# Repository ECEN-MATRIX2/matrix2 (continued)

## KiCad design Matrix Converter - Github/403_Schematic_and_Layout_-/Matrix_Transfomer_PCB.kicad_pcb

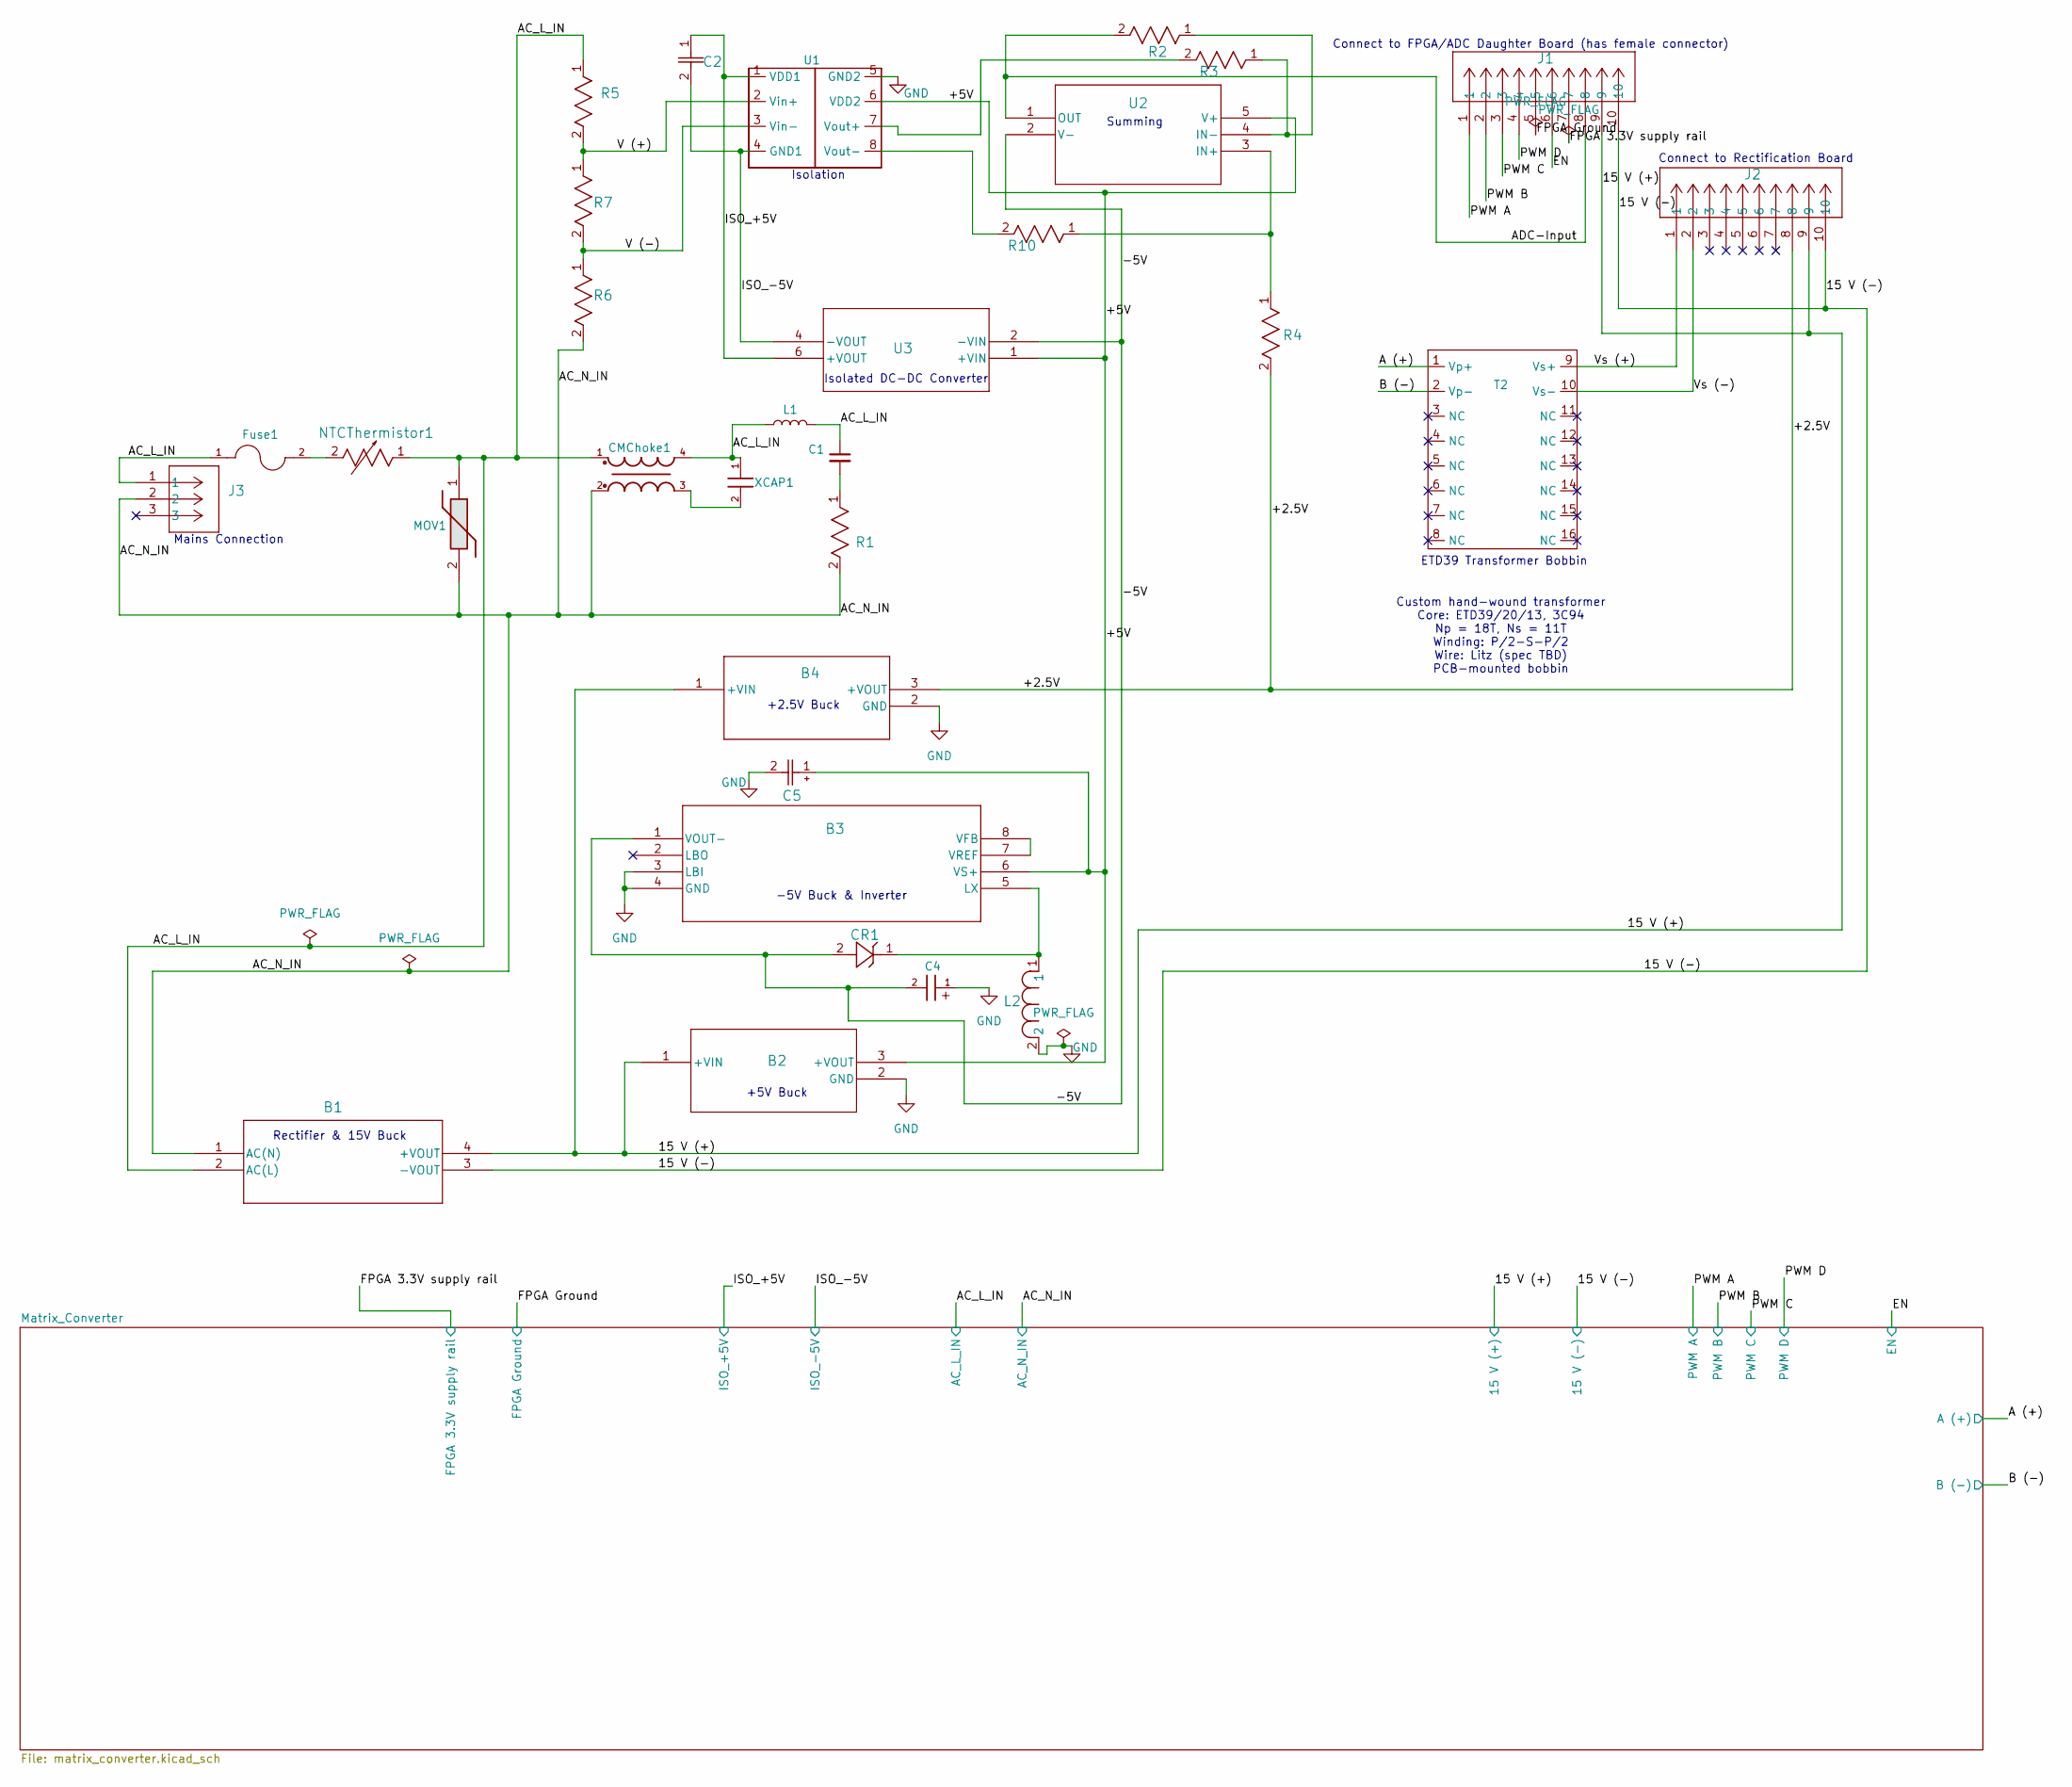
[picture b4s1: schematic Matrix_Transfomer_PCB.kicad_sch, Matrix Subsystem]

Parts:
B1: TMPS 10-115; TMPS10_TRP
B2: R-785.0-0.5; R-785.0-0.5_RCP
B3: MAX637AEPA+; 21-0043D_8_MXM
B4: R-78K2.5-2.0L; R-78K-2p0L_RCP
C1: MKP1840422104M; C_Rect_L26.5mm_W10.5mm_P22.50mm_MKS4
C2: K104K15X7RF5TL2; K104K15X7RF5TL2_VIS
C4: WCAP-ATG5_5X11; CAP_UBT_8X11P5_NCH
C5: UBW1E101MPD; CAP_UBT_8X11P5_NCH
CMChoke1: WE-CMB_S
CR1: 1N5819; DO-41_STM
Fuse1: 0HAAL1600-02; FUSRR508W60L840T400H810B; PARTREV Aug2024
J1, J2: 5104338-1; CONN_5104338-1_TYC
J3: 1985959; CONN_1985959_PXC
L1: 6100-472K-RC; Bourns_6100_Radial_Vertical_D11.0mm_P6.00mm
L2: PE-53117NL; IND_PE-53117NL_PUL
MOV1: TMOV14RP275EL2T7; Littelfuse_TMOV14RP275E; Mouser Part Number 576-TMOV14RP275EL2T7
NTCThermistor1: SL15 5R007; TRES_SL15 5R007_AMT
R1: RSF100JB-73-4R7; YAG_RSF100_YAG
R2, R3, R4, R10: MFR-25FRF52-10K; YAG_MF25_YAG
R5, R6: CF14JT2M40; STA_CF14_STP
R7: MFR-25FBF52-71K5; YAG_MF25_YAG
T2: XFMR_ETD39_CUSTOM; TDK_B66364W1016T001_ETD39_16Pin
U1: HCPL-7800A-000E; DIP-8_W7.62mm
U2: TLV9061IDBVR; DBV5_TEX
U3: RFB-0505S; RFB_RCP
XCAP1: WCAP-FTX2_P15_CS; WCAP-FTX2_P15L18W6H12_CS

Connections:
/15 V (+): B1.4 (+VOUT), B2.1 (+VIN), B4.1 (+VIN), J1.9, J2.9; also elsewhere on the board
/15 V (-): B1.3 (-VOUT), J1.10, J2.10; also elsewhere on the board
/+2.5V: B4.3 (+VOUT), J2.8, R4.2
/+5V: B2.3 (+VOUT), B3.6 (VS+), C5.1, U1.6 (VDD2), U2.5 (V+), U3.1 (+VIN)
/-5V: B3.1 (VOUT-), C4.2, CR1.2, U2.2 (V-), U3.2 (-VIN)
/A (+): T2.1 (Vp+); also elsewhere on the board
/AC_L_IN: B1.2 (AC(L)), C1.1, CMChoke1.1, CMChoke1.4, Fuse1.1, J3.1, L1.1, L1.2, MOV1.1, NTCThermistor1.1, R5.1, XCAP1.1; also elsewhere on the board
/AC_N_IN: B1.1 (AC(N)), CMChoke1.2, J3.2, MOV1.2, R1.2, R6.2; also elsewhere on the board
/ADC-Input: J1.8, R2.2, U2.1 (OUT)
/B (-): T2.2 (Vp-); also elsewhere on the board
/EN: J1.6; also elsewhere on the board
/FPGA 3.3V supply rail: J1.7; also elsewhere on the board
/FPGA Ground: J1.5; also elsewhere on the board
/ISO_+5V: C2.1, U1.1 (VDD1), U3.6 (+VOUT); also elsewhere on the board
/ISO_-5V: C2.2, U1.4 (GND1), U3.4 (-VOUT); also elsewhere on the board
/PWM A: J1.1; also elsewhere on the board
/PWM B: J1.2; also elsewhere on the board
/PWM C: J1.3; also elsewhere on the board
/PWM D: J1.4; also elsewhere on the board
/V (+): R5.2, R7.1, U1.2 (Vin+)
/V (-): R6.1, R7.2, U1.3 (Vin-)
/Vs (+): J2.1, T2.9 (Vs+)
/Vs (-): J2.2, T2.10 (Vs-)
GND: B2.2 (GND), B3.3 (LBI), B3.4 (GND), B4.2 (GND), C4.1, C5.2, L2.2, U1.5 (GND2)
unnamed: B3.5 (LX), CR1.1, L2.1
unnamed: B3.7 (VREF), B3.8 (VFB)
unnamed: C1.2, R1.1
unnamed: CMChoke1.3, XCAP1.2
unnamed: Fuse1.2, NTCThermistor1.2
unnamed: R3.2, U1.7 (Vout+)
unnamed: R10.2, U1.8 (Vout-)
unnamed: R4.1, R10.1, U2.3 (IN+)
unnamed: R2.1, R3.1, U2.4 (IN-)

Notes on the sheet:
ETD39 Transformer Bobbin
+5V Buck
Isolated DC-DC Converter
Connect to Rectification Board
Rectifier & 15V Buck
Custom hand-wound transformer Core: ETD39/20/13, 3C94 Np = 18T, Ns = 11T Winding: P/2-S-P/2 Wire: Litz (spec TBD) PCB-mounted bobbin
Connect to FPGA/ADC Daughter Board (has female connector)
+2.5V Buck
Isolation
-5V Buck & Inverter
Summing
Mains Connection

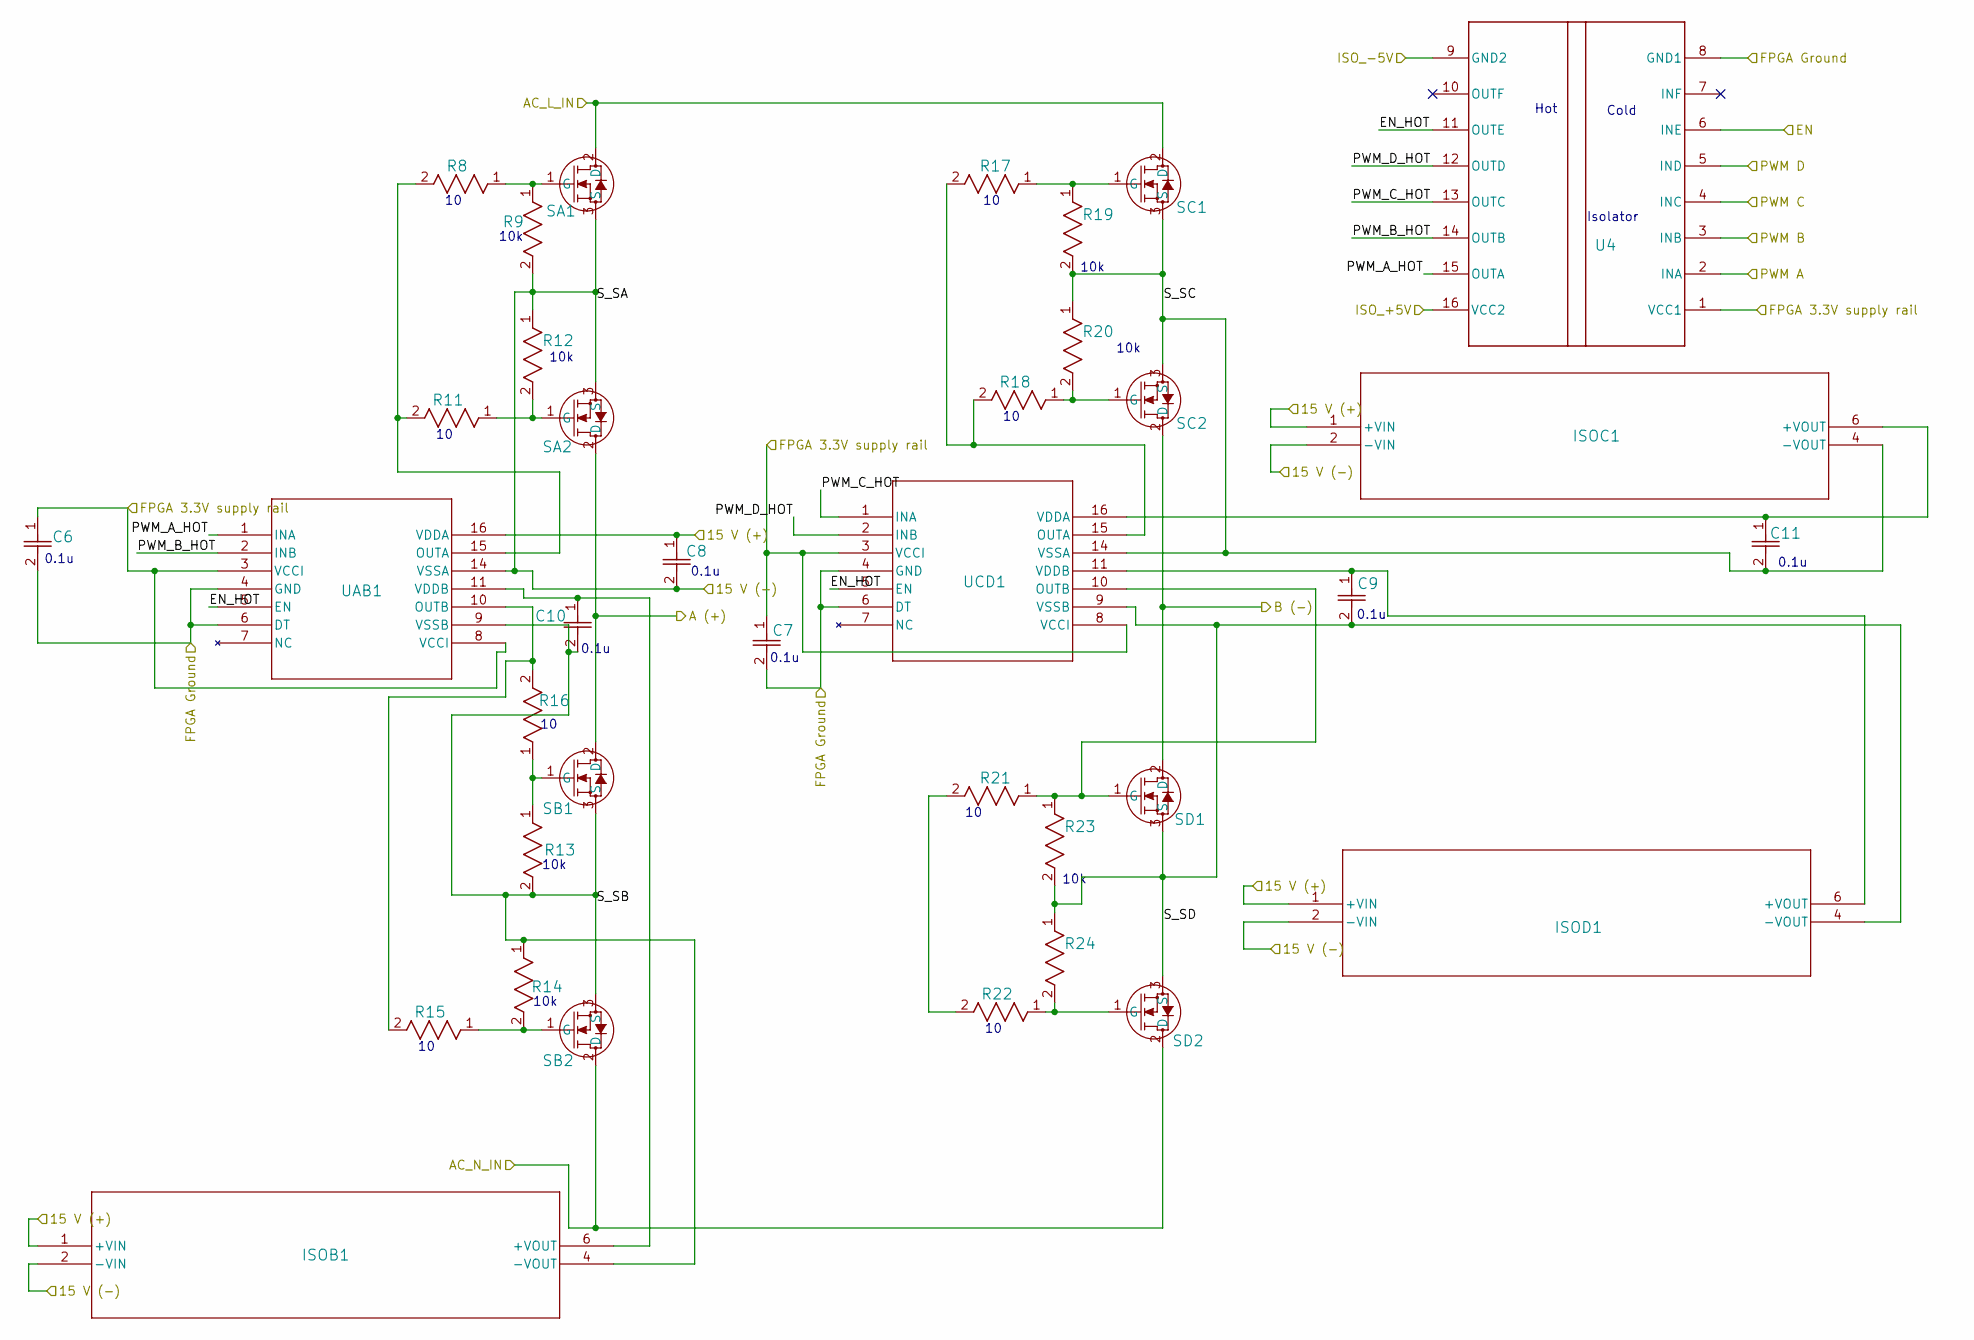
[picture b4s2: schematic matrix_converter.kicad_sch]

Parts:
C6, C7, C8, C9, C10, C11: K104K15X7RF5TL2; K104K15X7RF5TL2_VIS
ISOB1: TMA 1515S; TMA SINGLE_TRP
ISOC1: TMA 1515S; TMA SINGLE_TRP
ISOD1: TMA 1515S; TMA SINGLE_TRP
R8: RC0805FR-0710RL; RC0805N_YAG-L
R9, R12, R13, R14, R19, R20, R23, R24: MFR-25FRF52-10K; YAG_MF25_YAG
R11, R15, R16, R17, R18, R21, R22: RC0805FR-0710RL; RC0805N_YAG
SA1, SA2: C3M0075120D; TO-247-3_CRW
SB1, SB2: C3M0075120D; TO-247-3_CRW
SC1, SC2: C3M0075120D; TO-247-3_CRW
SD1, SD2: C3M0075120D; TO-247-3_CRW
U4: ISO7760FDWR; DW0016B_N
UAB1: UCC21530DWKR; SOIC14_7P6X10P5_TEX
UCD1: UCC21530DWKR; SOIC14_7P6X10P5_TEX

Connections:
/15 V (+): C8.1, ISOB1.1 (+VIN), ISOC1.1 (+VIN), ISOD1.1 (+VIN), UAB1.16 (VDDA); also elsewhere on the board
/15 V (-): C8.2, ISOB1.2 (-VIN), ISOC1.2 (-VIN), ISOD1.2 (-VIN), R9.2, R12.1, SA1.3 (S), SA2.3 (S), UAB1.14 (VSSA); also elsewhere on the board
/A (+): SA2.2 (D), SB1.2 (D); also elsewhere on the board
/AC_L_IN: SA1.2 (D), SC1.2 (D); also elsewhere on the board
/AC_N_IN: SB2.2 (D), SD2.2 (D); also elsewhere on the board
/B (-): SC2.2 (D), SD1.2 (D); also elsewhere on the board
/EN: U4.6 (INE); also elsewhere on the board
/FPGA 3.3V supply rail: C6.1, C7.1, U4.1 (VCC1), UAB1.3 (VCCI), UAB1.8 (VCCI), UCD1.3 (VCCI), UCD1.8 (VCCI); also elsewhere on the board
/FPGA Ground: C6.2, C7.2, U4.8 (GND1), UAB1.4 (GND), UAB1.6 (DT), UCD1.4 (GND), UCD1.6 (DT); also elsewhere on the board
/ISO_+5V: U4.16 (VCC2); also elsewhere on the board
/ISO_-5V: U4.9 (GND2); also elsewhere on the board
/Matrix_Converter/EN_HOT: U4.11 (OUTE), UAB1.5 (EN), UCD1.5 (EN)
/Matrix_Converter/PWM_A_HOT: U4.15 (OUTA), UAB1.1 (INA)
/Matrix_Converter/PWM_B_HOT: U4.14 (OUTB), UAB1.2 (INB)
/Matrix_Converter/PWM_C_HOT: U4.13 (OUTC), UCD1.1 (INA)
/Matrix_Converter/PWM_D_HOT: U4.12 (OUTD), UCD1.2 (INB)
/Matrix_Converter/S_SB: C10.2, ISOB1.4 (-VOUT), R13.2, R14.1, SB1.3 (S), SB2.3 (S), UAB1.9 (VSSB)
/Matrix_Converter/S_SC: C11.2, ISOC1.4 (-VOUT), R19.2, R20.1, SC1.3 (S), SC2.3 (S), UCD1.14 (VSSA)
/Matrix_Converter/S_SD: C9.2, ISOD1.4 (-VOUT), R23.2, R24.1, SD1.3 (S), SD2.3 (S), UCD1.9 (VSSB)
/PWM A: U4.2 (INA); also elsewhere on the board
/PWM B: U4.3 (INB); also elsewhere on the board
/PWM C: U4.4 (INC); also elsewhere on the board
/PWM D: U4.5 (IND); also elsewhere on the board
unnamed: C10.1, ISOB1.6 (+VOUT), UAB1.11 (VDDB)
unnamed: C11.1, ISOC1.6 (+VOUT), UCD1.16 (VDDA)
unnamed: C9.1, ISOD1.6 (+VOUT), UCD1.11 (VDDB)
unnamed: R21.2, R22.2
unnamed: R8.1, R9.1, SA1.1 (G)
unnamed: R11.1, R12.2, SA2.1 (G)
unnamed: R13.1, R16.1, SB1.1 (G)
unnamed: R14.2, R15.1, SB2.1 (G)
unnamed: R17.1, R19.1, SC1.1 (G)
unnamed: R18.1, R20.2, SC2.1 (G)
unnamed: R21.1, R23.1, SD1.1 (G), UCD1.10 (OUTB)
unnamed: R22.1, R24.2, SD2.1 (G)
unnamed: R8.2, R11.2, UAB1.15 (OUTA)
unnamed: R15.2, R16.2, UAB1.10 (OUTB)
unnamed: R17.2, R18.2, UCD1.15 (OUTA)

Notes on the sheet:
Hot
0.1u
Isolator
10k
Cold

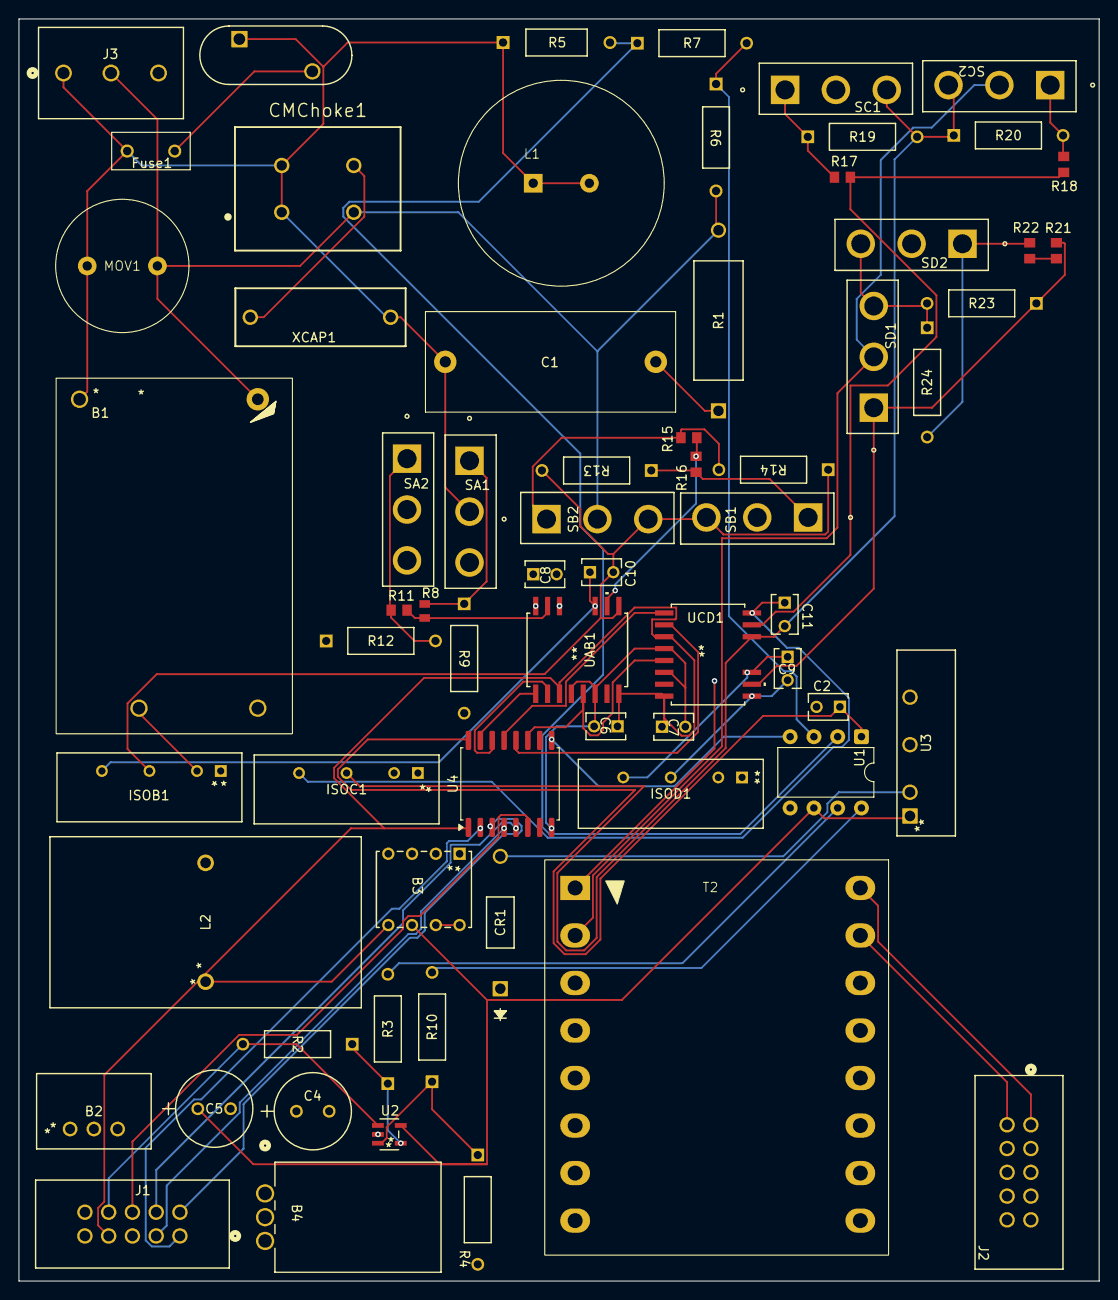
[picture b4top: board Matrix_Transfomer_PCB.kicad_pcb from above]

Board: 4 copper layers, 115.5 x 134.9 mm, 67 parts (0 on the bottom side), 56 nets.

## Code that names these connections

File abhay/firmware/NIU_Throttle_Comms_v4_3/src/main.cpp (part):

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static_assert(cfg::CURRENT_LIMIT_A==ThrottleMode::MAX_CURRENT_A,"Current request must match bench limit");

namespace pin {
constexpr uint32_t MISO=PB3,MOSI=PB4,SCK=PC10,NCS=PC9,ENABLE=PB5;
constexpr uint32_t UH=PA10,VH=PA9,WH=PA8,UL=PB15,VL=PB14,WL=PB13;
constexpr uint32_t FAULT=PB7,LED=PB0,H1=PC8,H2=PC7,H3=PC6;
constexpr uint32_t MOTOR_TEMP=PC4,PCB_TEMP=PA3,VM=PC3,MODE=PC13;
constexpr uint32_t CURRENT[3]={PC2,PC1,PC0};
}
namespace reg {
constexpr uint8_t GCONF=0x00,GSTAT=0x01,IOIN=0x04,SHORT_CONF=0x09,DRV_CONF=0x0A;
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static uint32_t controlBusUs=0;
static int zeroCurrent[3]={},zeroMinimum[3]={},zeroMaximum[3]={};
static control::Temperature motorTemp{false,NAN,NAN},pcbTemp{false,NAN,NAN};
static HardwareSerial motorLink(uint32_t(PB10)); // USART3 single-pin half duplex
static comms::Requests commRequests;
static bool remoteClearPermit=false;
static uint32_t remoteClearMs=0;
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    if(peak>=cfg::CURRENT_TRIP_A)trip(Fault::Overcurrent);
}
static void sampleThrottle() {
    readADC(PA6); // discard after changing ADC mux
    float a=readADC(PA6),b=readADC(PA6),c=readADC(PA6);
    throttle.sample(median3(a,b,c)*cfg::ADC_VREF/4095.0f,millis());
}
static bool startVoltage() {return isfinite(vin) && vin>=cfg::VM_START_MIN && vin<=cfg::VM_START_MAX;}
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
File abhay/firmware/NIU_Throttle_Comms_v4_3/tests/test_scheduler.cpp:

// Compile the ACTUAL comms.inc against a simulated UART/HAL, without hardware.
#include <cassert>
#include <deque>
#include <string>
#include "comms_protocol.h"
#include "throttle_mode.h"
#include "demo_battery.h"
constexpr int PA7=7,PA5=5,PB11=27,PA6=6,INPUT=0,GPIO_PIN_10=1024;
constexpr int GPIO_MODE_AF_OD=2,GPIO_NOPULL=0,GPIO_SPEED_FREQ_LOW=0,GPIO_AF7_USART3=7;
constexpr int USART3_IRQn=39,SERIAL_TX_BUFFER_SIZE=64,DAC_CR_EN2=1,USART_SR_TC=1;
struct {unsigned SR=USART_SR_TC;} uart;
auto USART3=&uart;
struct {unsigned CR=0;} dac;
auto DAC=&dac;
int gpio;auto GPIOB=&gpio;
struct GPIO_InitTypeDef {int Pin,Mode,Pull,Speed,Alternate;};
void pinMode(int,int) {}
void __HAL_RCC_DAC_CLK_ENABLE() {}
void HAL_GPIO_Init(int*,GPIO_InitTypeDef* p){assert(p->Mode==GPIO_MODE_AF_OD);}
void HAL_NVIC_SetPriority(int,int priority,int){assert(priority==2);}
struct FakeSerial {
    std::deque<char> tx,rx;std::string output;bool receive=true;
    unsigned reads=0,writes=0;
    void begin(unsigned baud){assert(baud==9600);}
    int availableForWrite(){return SERIAL_TX_BUFFER_SIZE-1-int(tx.size());}
    int available(){return int(rx.size());}
    void write(uint8_t c){assert(availableForWrite()>0);receive=false;uart.SR=0;tx.push_back(char(c));++writes;}
    void enableHalfDuplexRx(){assert(tx.empty() && (uart.SR&USART_SR_TC));receive=true;}
    int read(){assert(receive && tx.empty());char c=rx.front();rx.pop_front();++reads;return c;}
    void drain(){if(!tx.empty()){output+=tx.front();tx.pop_front();}if(tx.empty())uart.SR=USART_SR_TC;}
    void inject(const std::string& s){assert(receive);for(char c:s)rx.push_back(c);}
} motorLink;
struct Lock {Lock(){} ~Lock(){}};
enum class Fault {None=0,Overcurrent=6};
struct {bool running=false;Fault fault=Fault::None;} drive;
static ThrottleMode throttle;
static DemoBattery demoBattery;
static comms::Requests commRequests;
static uint32_t clockMs=0,lastCommMs=0,commSequence=0,currentSampleMs=0,vmReadUs=0;
static bool currentSampleValid=false,currentCalibrated=false,speedValid=true;
static bool driverReady=false,faultIrq=false;
static unsigned vmAdc=3000;
static float vin=36,currentFiltered=0,dutyPct=0,measuredMph=0;
static struct {bool valid=false;float vm=0,amps=0;} faultSnapshot;
uint32_t micros(){return clockMs*1000;}
bool charging(){return false;}
bool waitTorque=false;
comms::State stateCode(){return drive.fault!=Fault::None?comms::Faulted:(waitTorque?comms::WaitTorque:comms::Stopped);}
static unsigned clears=0;
comms::Result clearFaultRequest(){++clears;drive.fault=Fault::None;throttle.stop();return comms::Cleared;}
comms::Result handleRemoteCommand(comms::Command c){assert(c.action==comms::Reset);return clearFaultRequest();}
#include "../src/comms.inc"
static void tick(){++clockMs;vmReadUs=micros();motorLink.drain();serviceComms(clockMs);}
static void nextSlot(){
    auto previous=commRequests.token;
    for(unsigned n=0;n<1000;++n){tick();if(commRequests.active(clockMs) && commRequests.token!=previous)return;}
    assert(false);
}
static std::string request(uint32_t token,uint32_t id){
    char line[64];auto n=comms::encodeCommand({token,id},line,sizeof(line));return {line,n};
}
int main(){
    beginCommUart();nextSlot();
    assert(motorLink.receive && motorLink.output.back()=='\n');
    auto end=motorLink.output.size();auto start=motorLink.output.rfind('$');
    comms::Status status;
    assert(comms::decode(motorLink.output.data()+start,end-start,status));
    assert(status.data.sequence==commRequests.token);
    drive.fault=Fault::Overcurrent;
    motorLink.inject(request(commRequests.token,1));
    auto reads=motorLink.reads;serviceComms(clockMs);assert(motorLink.reads-reads<=32);
    serviceComms(clockMs);assert(clears==1 && commRequests.lastResult==comms::Cleared);
    assert(!throttle.requested && !throttle.armed);
    motorLink.inject(request(commRequests.token,2));serviceComms(clockMs);serviceComms(clockMs);
    assert(clears==1); // second request in same slot rejected
    nextSlot();drive.fault=Fault::Overcurrent;
    motorLink.inject(request(commRequests.token,1));serviceComms(clockMs);serviceComms(clockMs);
    assert(clears==1 && drive.fault==Fault::Overcurrent); // cached ACK cannot clear new fault
    nextSlot();
    motorLink.inject(request(commRequests.token-1,2));serviceComms(clockMs);serviceComms(clockMs);
    assert(clears==1);
    clockMs=commRequests.openedAt+comms::RX_WINDOW_MS;
    motorLink.inject(request(commRequests.token,2));serviceComms(clockMs);serviceComms(clockMs);
    assert(clears==1); // late packet rejected
    nextSlot(); // verify subsequent status still shows fault and previous ACK
    end=motorLink.output.size();start=motorLink.output.rfind('$');
    assert(comms::decode(motorLink.output.data()+start,end-start,status));
    assert(status.data.fault==6 && status.ackId==1 && status.ackResult==comms::Cleared);
    drive.fault=Fault::None;waitTorque=true;nextSlot();
    end=motorLink.output.size();start=motorLink.output.rfind('$');
    assert(comms::decode(motorLink.output.data()+start,end-start,status));
    assert(status.state==comms::WaitTorque && !(status.data.flags&telemetry::FAULT));
    // Stalled TX hardware does not cause a blocking flush/read/write call.
    clockMs+=300;serviceComms(clockMs);assert(commSending);
    for(unsigned i=0;i<10000;++i)serviceComms(clockMs);
    assert(!motorLink.tx.empty() && !commRequests.active(clockMs));
    puts("PASS: actual UART scheduler with simulated backpressure, turnaround, ACK, duplicate, stale and late packets");
}
